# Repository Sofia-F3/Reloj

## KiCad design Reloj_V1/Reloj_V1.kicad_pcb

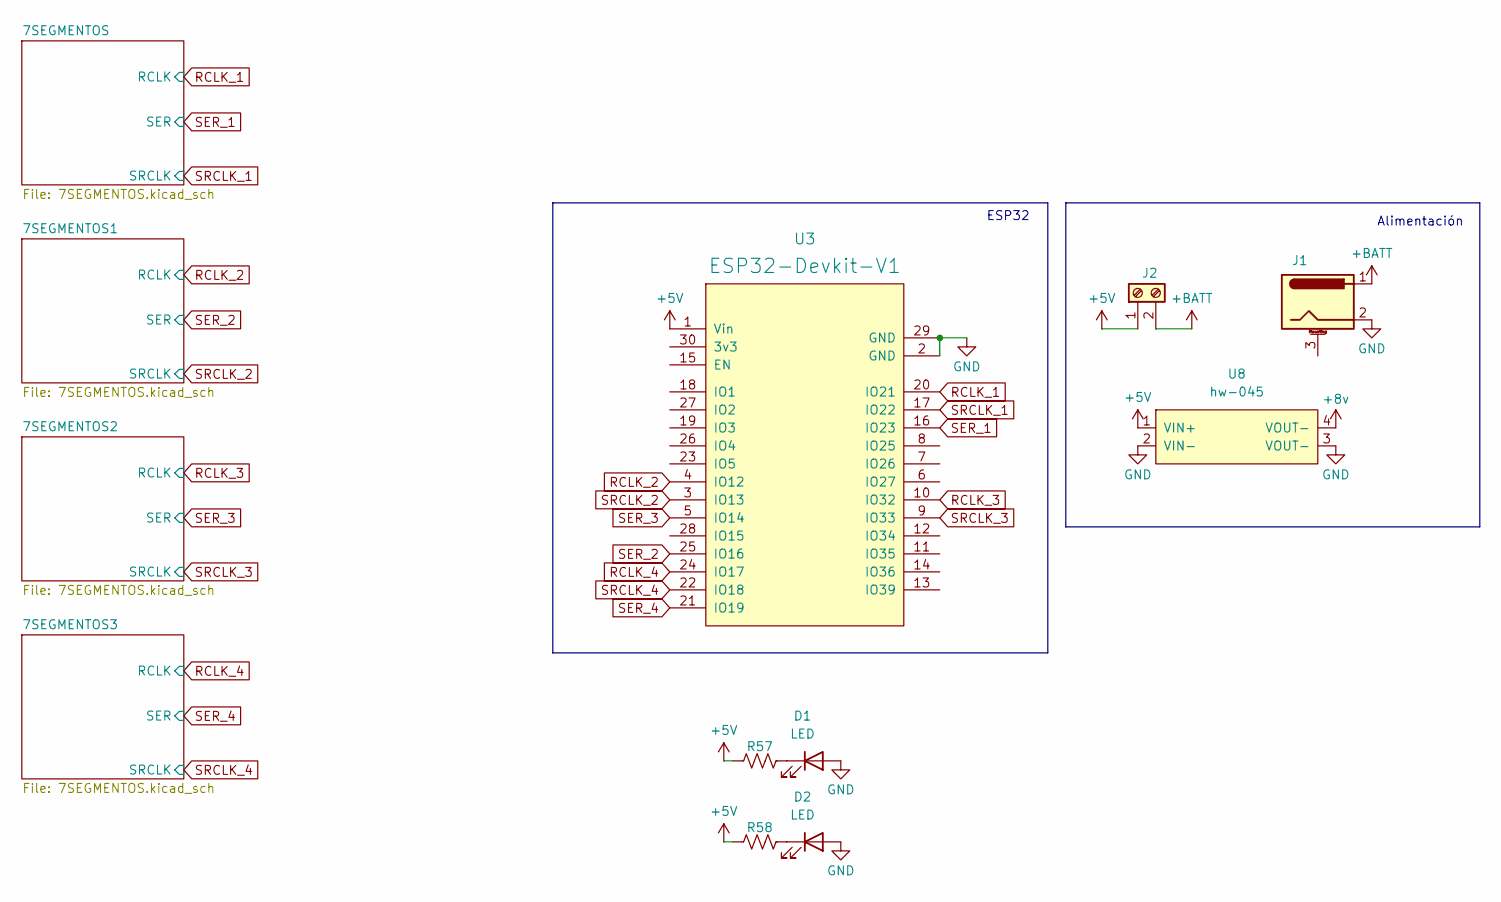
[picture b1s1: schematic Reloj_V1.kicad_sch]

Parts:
D1, D2: LED; LED_D5.0mm
J1: Barrel_Jack_MountingPin; BarrelJack_Horizontal
J2: Screw_Terminal_01x02; TerminalBlock_Phoenix_MKDS-1,5-2-5.08_1x02_P5.08mm_Horizont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
R57, R58: R_US; R_1206_3216Metric_Pad1.30x1.75mm_HandSolder
U3: ESP32-Devkit-V1; DOIT_ESP32_Devkit
U8: hw-045

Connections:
+5V: J2.1, R57.1, R58.1, U3.1 (Vin), U8.1 (VIN+); also elsewhere on the board
+BATT: J1.1, J2.2
unnamed: D1.1 (K), R57.2
unnamed: D2.1 (K), R58.2
RCLK_1: U3.20 (IO21); also elsewhere on the board
RCLK_2: U3.4 (IO12); also elsewhere on the board
RCLK_3: U3.10 (IO32); also elsewhere on the board
RCLK_4: U3.24 (IO17); also elsewhere on the board
SER_1: U3.16 (IO23); also elsewhere on the board
SER_2: U3.25 (IO16); also elsewhere on the board
SER_3: U3.5 (IO14); also elsewhere on the board
SER_4: U3.21 (IO19); also elsewhere on the board
SRCLK_1: U3.17 (IO22); also elsewhere on the board
SRCLK_2: U3.3 (IO13); also elsewhere on the board
SRCLK_3: U3.9 (IO33); also elsewhere on the board
SRCLK_4: U3.22 (IO18); also elsewhere on the board

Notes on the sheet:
ESP32
Alimentación

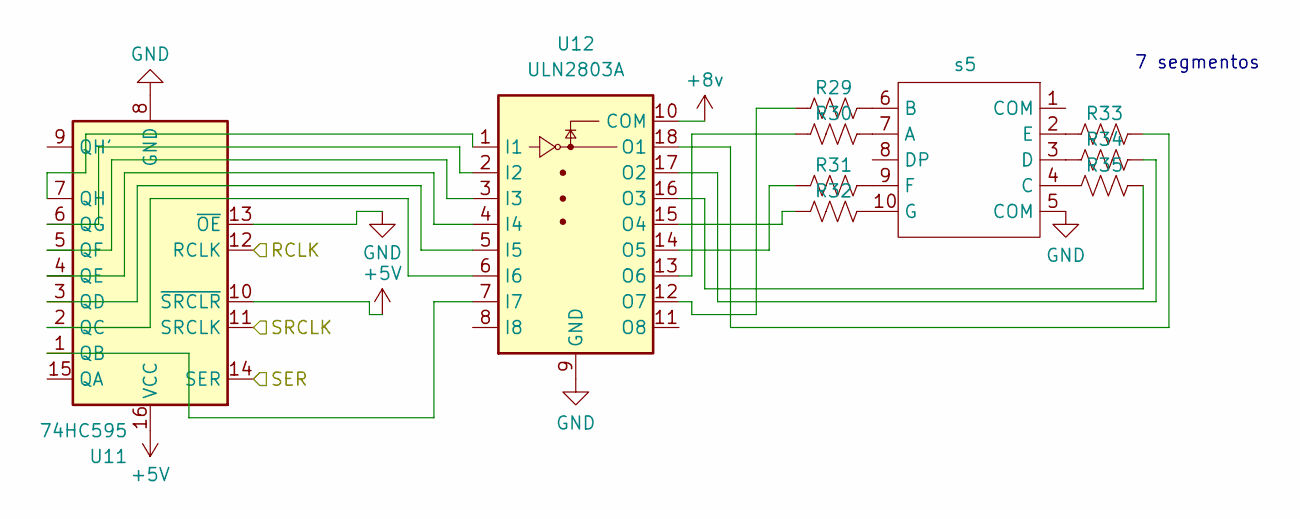
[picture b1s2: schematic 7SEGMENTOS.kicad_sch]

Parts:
R29, R30, R31, R32, R33, R34, R35: R_US; R_Axial_DIN0207_L6.3mm_D2.5mm_P10.16mm_Horizontal
U11: 74HC595; DIP-16_W7.62mm_LongPads
U12: ULN2803A; DIP-18_W7.62mm_LongPads
s5: LED-SEG-TH_C1801E-GW

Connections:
+5V: U11.10 (~SRCLR), U11.16 (VCC); also elsewhere on the board
unnamed: U11.1 (QB), U12.7 (I7)
unnamed: U11.2 (QC), U12.6 (I6)
unnamed: U11.3 (QD), U12.5 (I5)
unnamed: U11.4 (QE), U12.4 (I4)
unnamed: U11.5 (QF), U12.3 (I3)
unnamed: U11.6 (QG), U12.2 (I2)
unnamed: U11.7 (QH), U12.1 (I1)
unnamed: R33.2, U12.18 (O1)
unnamed: R34.2, U12.17 (O2)
unnamed: R35.2, U12.16 (O3)
unnamed: R32.1, U12.15 (O4)
unnamed: R31.1, U12.14 (O5)
unnamed: R30.1, U12.13 (O6)
unnamed: R29.1, U12.12 (O7)
unnamed: R30.2, s5.7 (A)
unnamed: R29.2, s5.6 (B)
unnamed: R35.1, s5.4 (C)
unnamed: R34.1, s5.3 (D)
unnamed: R33.1, s5.2 (E)
unnamed: R31.2, s5.9 (F)
unnamed: R32.2, s5.10 (G)
RCLK_1: U11.12 (RCLK); also elsewhere on the board
SER_1: U11.14 (SER); also elsewhere on the board
SRCLK_1: U11.11 (SRCLK); also elsewhere on the board

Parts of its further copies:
R36, R37, R38, R39, R40, R41, R42, R43, R44, R45, R46, R47, R48, R49, R50, R51, R52, R53, R54, R55, R56: R_US; R_Axial_DIN0207_L6.3mm_D2.5mm_P10.16mm_Horizontal
U13, U15, U17: 74HC595; DIP-16_W7.62mm_LongPads
U14, U16, U18: ULN2803A; DIP-18_W7.62mm_LongPads
s6, s7, s8: LED-SEG-TH_C1801E-GW

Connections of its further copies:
+5V: U13.10 (~SRCLR), U13.16 (VCC), U15.10 (~SRCLR), U15.16 (VCC), U17.10 (~SRCLR), U17.16 (VCC); also elsewhere on the board
unnamed: U13.1 (QB), U14.7 (I7)
unnamed: U13.2 (QC), U14.6 (I6)
unnamed: U13.3 (QD), U14.5 (I5)
unnamed: U13.4 (QE), U14.4 (I4)
unnamed: U13.5 (QF), U14.3 (I3)
unnamed: U13.6 (QG), U14.2 (I2)
unnamed: U13.7 (QH), U14.1 (I1)
unnamed: R40.2, U14.18 (O1)
unnamed: R41.2, U14.17 (O2)
unnamed: R42.2, U14.16 (O3)
unnamed: R39.1, U14.15 (O4)
unnamed: R38.1, U14.14 (O5)
unnamed: R37.1, U14.13 (O6)
unnamed: R36.1, U14.12 (O7)
unnamed: U15.1 (QB), U16.7 (I7)
unnamed: U15.2 (QC), U16.6 (I6)
unnamed: U15.3 (QD), U16.5 (I5)
unnamed: U15.4 (QE), U16.4 (I4)
unnamed: U15.5 (QF), U16.3 (I3)
unnamed: U15.6 (QG), U16.2 (I2)
unnamed: U15.7 (QH), U16.1 (I1)
unnamed: R47.2, U16.18 (O1)
unnamed: R48.2, U16.17 (O2)
unnamed: R49.2, U16.16 (O3)
unnamed: R46.1, U16.15 (O4)
unnamed: R45.1, U16.14 (O5)
unnamed: R44.1, U16.13 (O6)
unnamed: R43.1, U16.12 (O7)
unnamed: U17.1 (QB), U18.7 (I7)
unnamed: U17.2 (QC), U18.6 (I6)
unnamed: U17.3 (QD), U18.5 (I5)
unnamed: U17.4 (QE), U18.4 (I4)
unnamed: U17.5 (QF), U18.3 (I3)
unnamed: U17.6 (QG), U18.2 (I2)
unnamed: U17.7 (QH), U18.1 (I1)
unnamed: R54.2, U18.18 (O1)
unnamed: R55.2, U18.17 (O2)
unnamed: R56.2, U18.16 (O3)
unnamed: R53.1, U18.15 (O4)
unnamed: R52.1, U18.14 (O5)
unnamed: R51.1, U18.13 (O6)
unnamed: R50.1, U18.12 (O7)
unnamed: R37.2, s6.7 (A)
unnamed: R36.2, s6.6 (B)
unnamed: R42.1, s6.4 (C)
unnamed: R41.1, s6.3 (D)
unnamed: R40.1, s6.2 (E)
unnamed: R38.2, s6.9 (F)
unnamed: R39.2, s6.10 (G)
unnamed: R44.2, s7.7 (A)
unnamed: R43.2, s7.6 (B)
unnamed: R49.1, s7.4 (C)
unnamed: R48.1, s7.3 (D)
unnamed: R47.1, s7.2 (E)
unnamed: R45.2, s7.9 (F)
unnamed: R46.2, s7.10 (G)
unnamed: R51.2, s8.7 (A)
unnamed: R50.2, s8.6 (B)
unnamed: R56.1, s8.4 (C)
unnamed: R55.1, s8.3 (D)
unnamed: R54.1, s8.2 (E)
unnamed: R52.2, s8.9 (F)
unnamed: R53.2, s8.10 (G)
RCLK_2: U13.12 (RCLK); also elsewhere on the board
RCLK_3: U15.12 (RCLK); also elsewhere on the board
RCLK_4: U17.12 (RCLK); also elsewhere on the board
SER_2: U13.14 (SER); also elsewhere on the board
SER_3: U15.14 (SER); also elsewhere on the board
SER_4: U17.14 (SER); also elsewhere on the board
SRCLK_2: U13.11 (SRCLK); also elsewhere on the board
SRCLK_3: U15.11 (SRCLK); also elsewhere on the board
SRCLK_4: U17.11 (SRCLK); also elsewhere on the board

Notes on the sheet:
7 segmentos

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
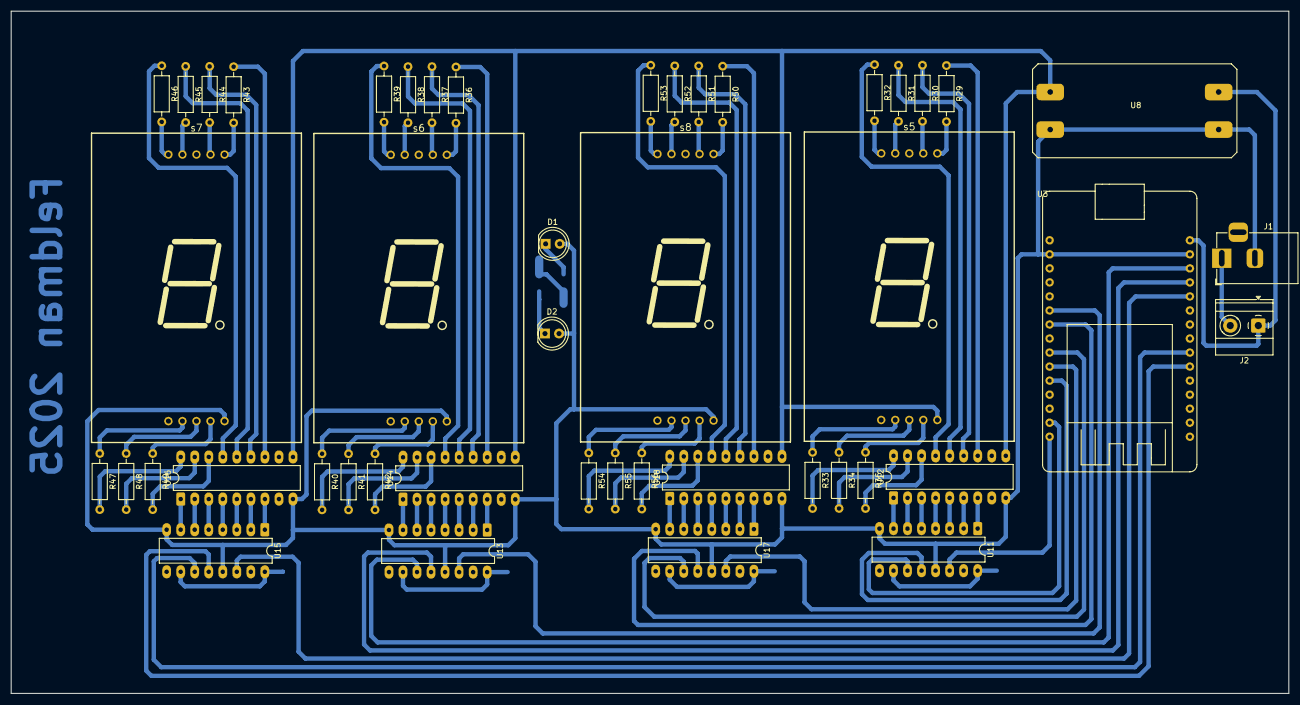
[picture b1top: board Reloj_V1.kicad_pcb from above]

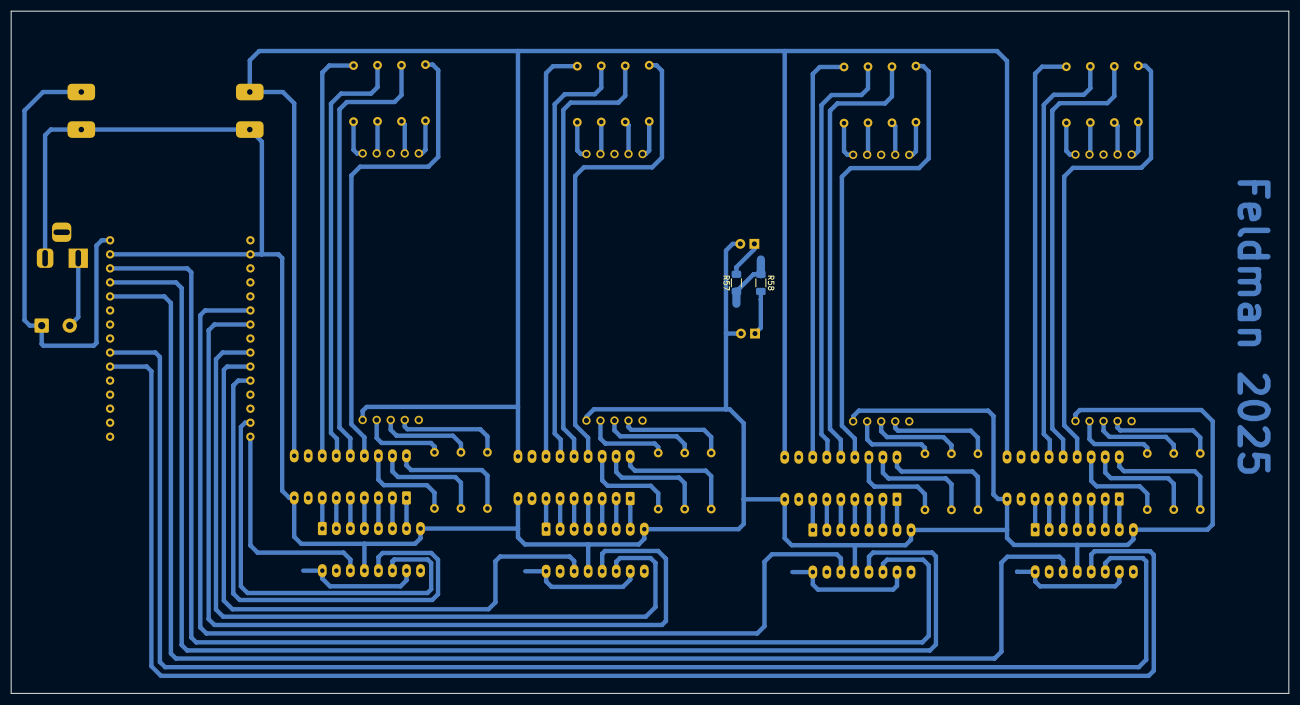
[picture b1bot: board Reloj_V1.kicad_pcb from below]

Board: 2 copper layers, 231.3 x 123.5 mm, 48 parts (2 on the bottom side), 102 nets.
